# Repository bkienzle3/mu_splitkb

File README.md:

# mu_splitkb
Mu Split Keyboard - 36-key columnar staggered split keyboard

## Firmware

Firmware is located in qmk_firmware. I'm planning to have this added into the official repo.
Keymaps are based on Miryoku (manna-harbour/miryoku), with my own customizations, of course.

## Bill of materials

Kailh Choc V1 key switches x 36
<br>Kailh Choc V1 Hotswap sockets x 36
<br>Elite-C/ProMicro x 2
<br>1N4148 MiniMELF diode x 36
<br>TM5RF-4450 x 2
<br>4P4C cable x 1

## Inspiration

While this keyboard was created from scratch, it was heavily inspired by the Sweep (davidphilipbarr/Sweep).

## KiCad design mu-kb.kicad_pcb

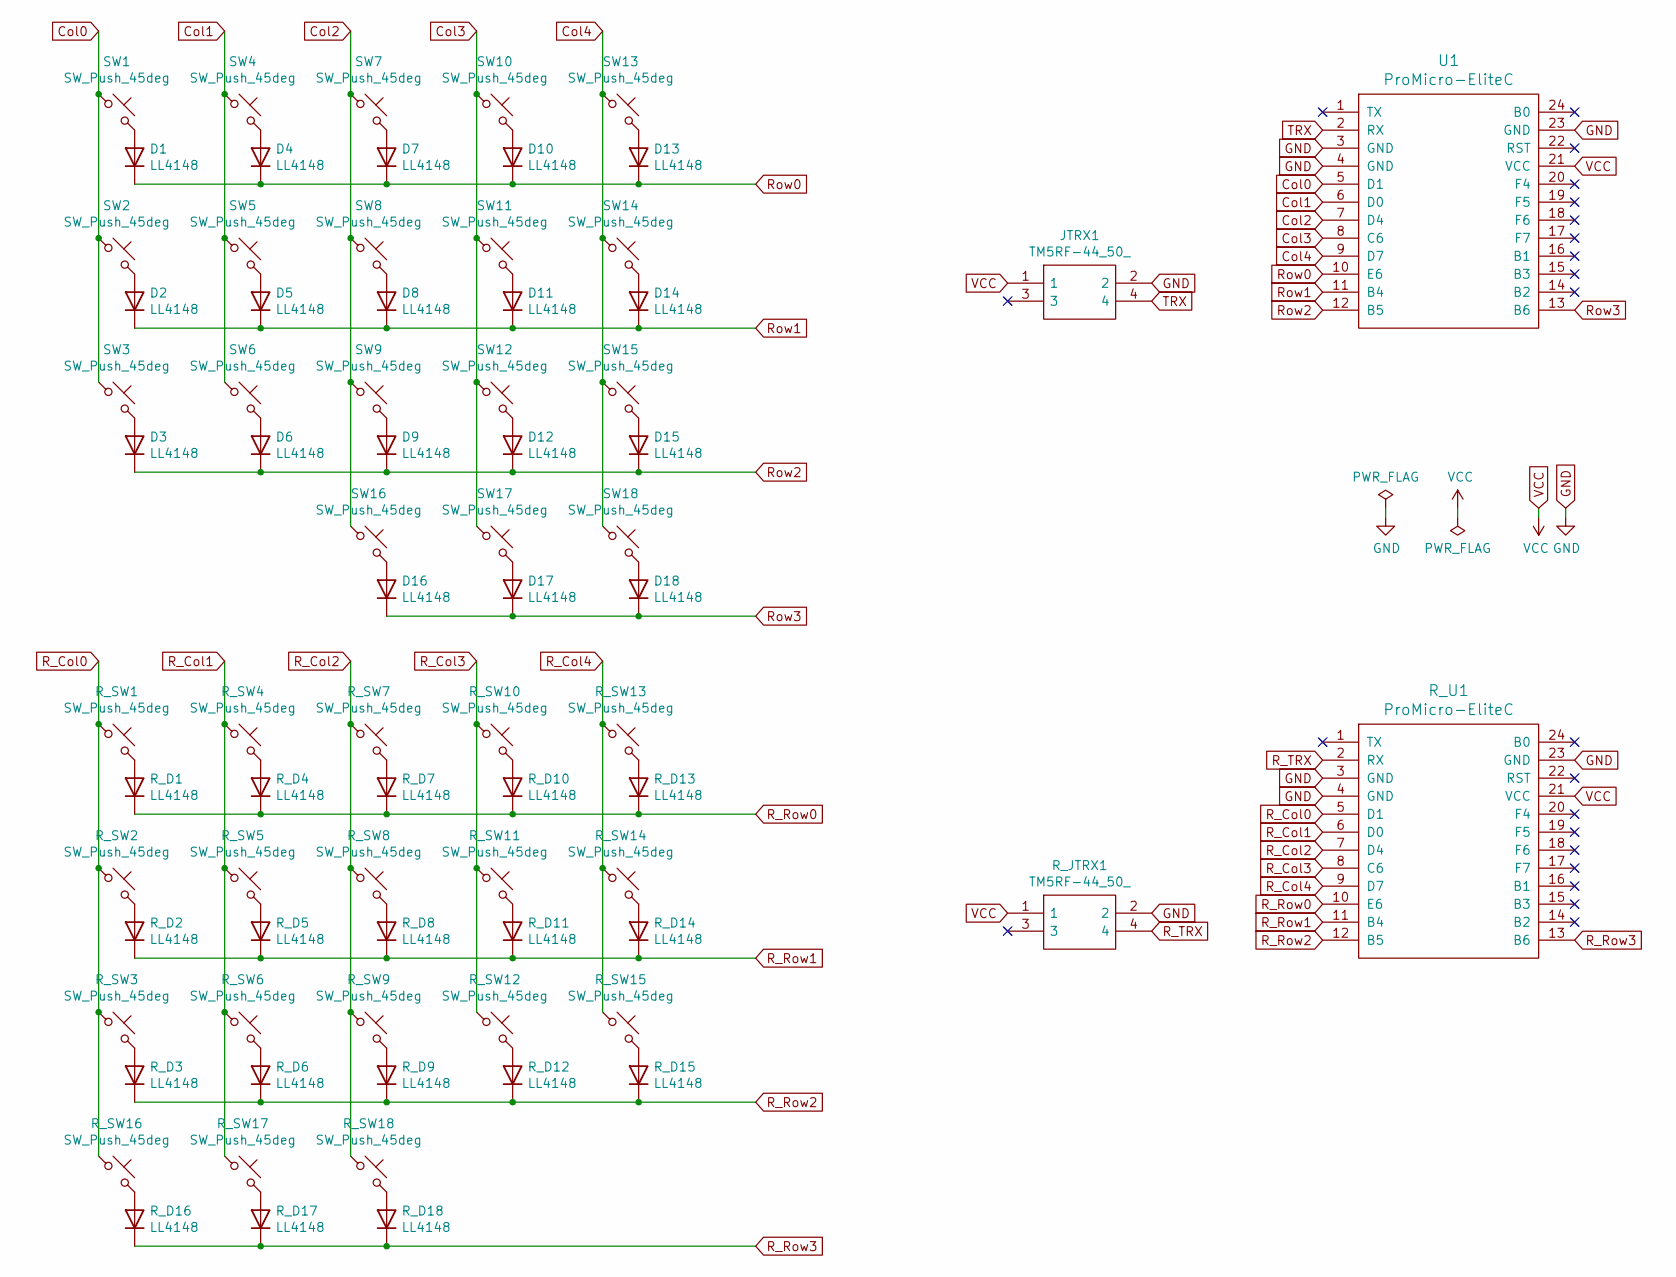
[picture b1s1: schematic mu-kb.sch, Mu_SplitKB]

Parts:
D1, D2, D3, D4, D5, D6, D7, D8, D9, D10, D11, D12, D13, D14, D15, D16, D17, D18: LL4148; D_MiniMELF
JTRX1: TM5RF-44_50_; TM5RF4450; Manufacturer_Part_Number TM5RF-44(50); Mouser Part Number 798-TM5RF4450
R_D1, R_D2, R_D3, R_D4, R_D5, R_D6, R_D7, R_D8, R_D9, R_D10, R_D11, R_D12, R_D13, R_D14, R_D15, R_D16, R_D17, R_D18: LL4148; D_MiniMELF
R_JTRX1: TM5RF-44_50_; TM5RF4450; Manufacturer_Part_Number TM5RF-44(50); Mouser Part Number 798-TM5RF4450
R_SW1, R_SW2, R_SW3, R_SW4, R_SW5, R_SW6, R_SW7, R_SW8, R_SW9, R_SW10, R_SW11, R_SW12, R_SW13, R_SW14, R_SW15, R_SW16, R_SW17, R_SW18: SW_Push_45deg; SW_Hotswap_Kailh_Choc_V1
R_U1: ProMicro-EliteC; ProMicro
SW1, SW2, SW3, SW4, SW5, SW6, SW7, SW8, SW9, SW10, SW11, SW12, SW13, SW14, SW15, SW16, SW17, SW18: SW_Push_45deg; SW_Hotswap_Kailh_Choc_V1
U1: ProMicro-EliteC; ProMicro

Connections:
Col0: SW1.1, SW2.1, SW3.1, U1.5 (D1)
Col1: SW4.1, SW5.1, SW6.1, U1.6 (D0)
Col2: SW7.1, SW8.1, SW9.1, SW16.1, U1.7 (D4)
Col3: SW10.1, SW11.1, SW12.1, SW17.1, U1.8 (C6)
Col4: SW13.1, SW14.1, SW15.1, SW18.1, U1.9 (D7)
GND: JTRX1.2, R_JTRX1.2, R_U1.3 (GND), R_U1.4 (GND), R_U1.23 (GND), U1.3 (GND), U1.4 (GND), U1.23 (GND)
unnamed: D1.2 (A), SW1.2
unnamed: D2.2 (A), SW2.2
unnamed: D3.2 (A), SW3.2
unnamed: D4.2 (A), SW4.2
unnamed: D5.2 (A), SW5.2
unnamed: D6.2 (A), SW6.2
unnamed: D7.2 (A), SW7.2
unnamed: D8.2 (A), SW8.2
unnamed: D9.2 (A), SW9.2
unnamed: D10.2 (A), SW10.2
unnamed: D11.2 (A), SW11.2
unnamed: D12.2 (A), SW12.2
unnamed: D13.2 (A), SW13.2
unnamed: D14.2 (A), SW14.2
unnamed: D15.2 (A), SW15.2
unnamed: D16.2 (A), SW16.2
unnamed: D17.2 (A), SW17.2
unnamed: D18.2 (A), SW18.2
unnamed: R_D1.2 (A), R_SW1.2
unnamed: R_D2.2 (A), R_SW2.2
unnamed: R_D3.2 (A), R_SW3.2
unnamed: R_D4.2 (A), R_SW4.2
unnamed: R_D5.2 (A), R_SW5.2
unnamed: R_D6.2 (A), R_SW6.2
unnamed: R_D7.2 (A), R_SW7.2
unnamed: R_D8.2 (A), R_SW8.2
unnamed: R_D9.2 (A), R_SW9.2
unnamed: R_D10.2 (A), R_SW10.2
unnamed: R_D11.2 (A), R_SW11.2
unnamed: R_D12.2 (A), R_SW12.2
unnamed: R_D13.2 (A), R_SW13.2
unnamed: R_D14.2 (A), R_SW14.2
unnamed: R_D15.2 (A), R_SW15.2
unnamed: R_D16.2 (A), R_SW16.2
unnamed: R_D17.2 (A), R_SW17.2
unnamed: R_D18.2 (A), R_SW18.2
R_Col0: R_SW1.1, R_SW2.1, R_SW3.1, R_SW16.1, R_U1.5 (D1)
R_Col1: R_SW4.1, R_SW5.1, R_SW6.1, R_SW17.1, R_U1.6 (D0)
R_Col2: R_SW7.1, R_SW8.1, R_SW9.1, R_SW18.1, R_U1.7 (D4)
R_Col3: R_SW10.1, R_SW11.1, R_SW12.1, R_U1.8 (C6)
R_Col4: R_SW13.1, R_SW14.1, R_SW15.1, R_U1.9 (D7)
R_Row0: R_D1.1 (K), R_D4.1 (K), R_D7.1 (K), R_D10.1 (K), R_D13.1 (K), R_U1.10 (E6)
R_Row1: R_D2.1 (K), R_D5.1 (K), R_D8.1 (K), R_D11.1 (K), R_D14.1 (K), R_U1.11 (B4)
R_Row2: R_D3.1 (K), R_D6.1 (K), R_D9.1 (K), R_D12.1 (K), R_D15.1 (K), R_U1.12 (B5)
R_Row3: R_D16.1 (K), R_D17.1 (K), R_D18.1 (K), R_U1.13 (B6)
R_TRX: R_JTRX1.4, R_U1.2 (RX)
Row0: D1.1 (K), D4.1 (K), D7.1 (K), D10.1 (K), D13.1 (K), U1.10 (E6)
Row1: D2.1 (K), D5.1 (K), D8.1 (K), D11.1 (K), D14.1 (K), U1.11 (B4)
Row2: D3.1 (K), D6.1 (K), D9.1 (K), D12.1 (K), D15.1 (K), U1.12 (B5)
Row3: D16.1 (K), D17.1 (K), D18.1 (K), U1.13 (B6)
TRX: JTRX1.4, U1.2 (RX)
VCC: JTRX1.1, R_JTRX1.1, R_U1.21 (VCC), U1.21 (VCC)

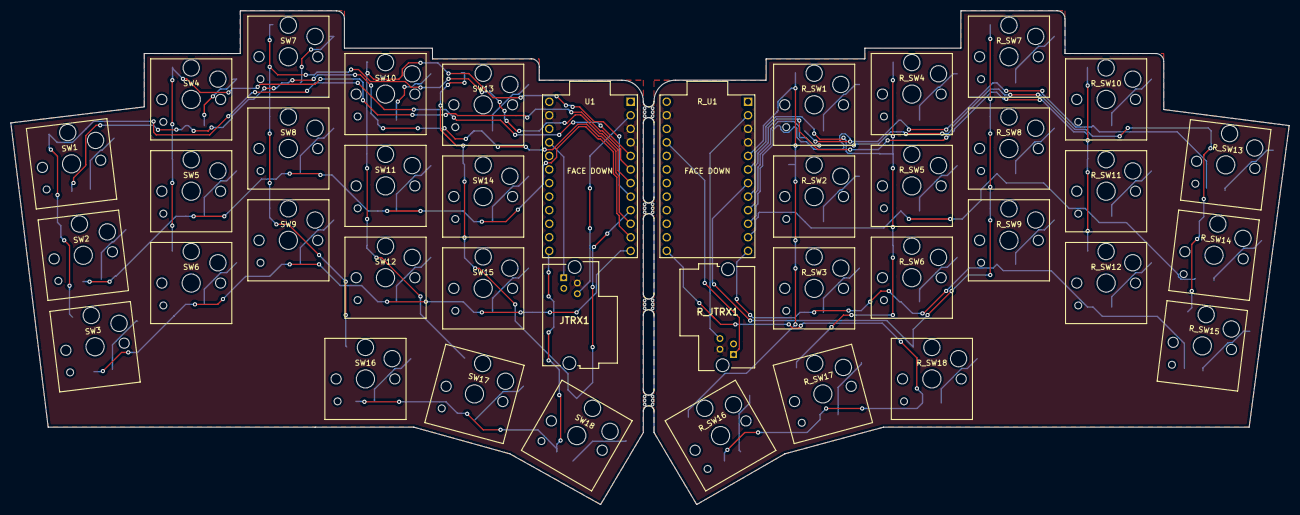
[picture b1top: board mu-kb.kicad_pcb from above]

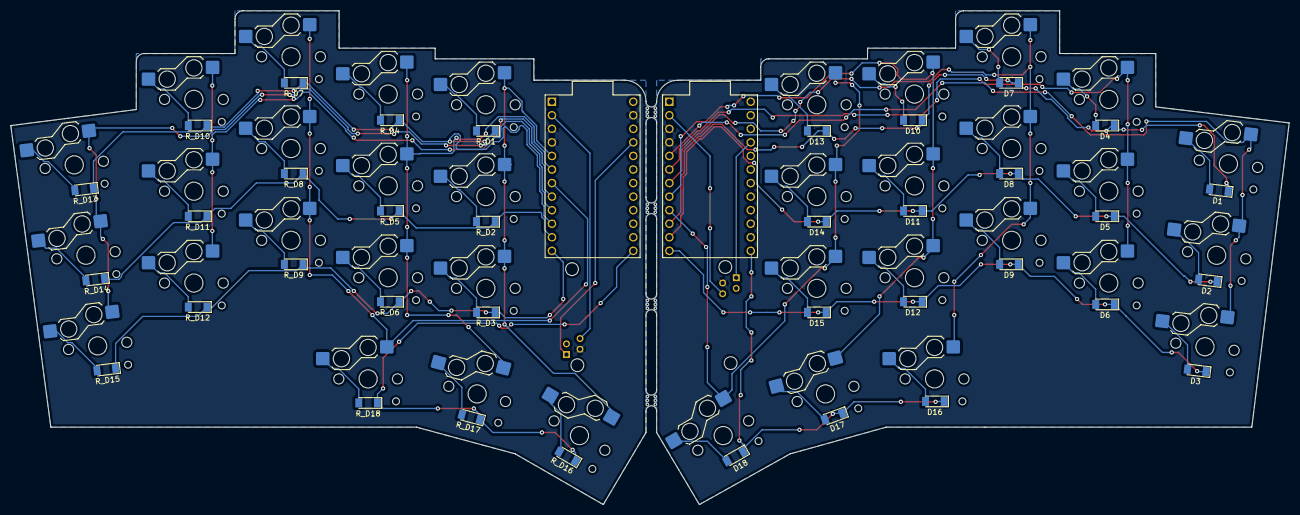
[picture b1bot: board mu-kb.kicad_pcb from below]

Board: 2 copper layers, 239.5 x 92.5 mm, 80 parts (36 on the bottom side), 58 nets.

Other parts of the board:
mouse-bite-2mm-slot, mouse-bite-2mm-slot#2, mouse-bite-2mm-slot#3, mouse-bite-2mm-slot#4: VAL**; mouse-bite-2mm-slot

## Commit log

2024-11-01 completed v2
2024-11-14 cleanup directories
2024-11-15 add qmk firmware
2024-11-27 modify f layer
2024-11-27 fix mediakeys
2024-12-10 add gaming mode
2024-12-13 add nkro
2024-12-13 adjust fps layer
